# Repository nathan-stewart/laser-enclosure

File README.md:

# Laser Enclosure Fire Control Diagrams

This repository contains Graphviz DOT diagrams for documenting the fire suppression logic and relay control layout in a Raspberry Pi-controlled laser enclosure project.

## Included Files

### `fire_state_machine.dot`
- Describes the FIRE state logic.
- **ARMED**: Tank is pressurized (system ready).
- **FIRE**: Triggered by pressure drop, CO₂ valve opens, gates close.
- **RESET**: Performed via E-stop twist.
- Use `dot -Tpng fire_state_machine.dot -o fire_state_machine.png` to render.

### `power_distribution.dot`
- Updated relay layout with sequential relay numbering:
  - `K1`: Laser
  - `K2`: High Pressure Air (HPA)
  - `K3`: CO₂ Valve
  - `K4`: Blast Gates (intake/exhaust)
  - `K5`: Low Pressure Air (LPA)
  - `K6`: Heater Fan
  - `K7`: Exhaust Fan
  - `K8`: PTC Heater (AC)
- Use `dot -Tpng relay_layout_k3_k4_separated.dot -o relay_layout_k3_k4_separated.png` to render.

## Notes

- Gates are gravity-closing and do not remain activated after a FIRE event.
- CO₂ valve remains open until a manual reset is performed.
- The system arms based on tank pressure and triggers on pressure drop.
- Relays are powered from 24V, 12V, and AC lines as appropriate.

## Rendering

Install [Graphviz](https://graphviz.org/download/) and run:

```bash
dot -Tpng fire_state_machine.dot -o fire_state_machine.png
dot -Tpng power_distribution.dot -o power_distribution.png
```

Or use online editors like [edotor.net](https://edotor.net/) or [dreampuf.github.io](https://dreampuf.github.io/GraphvizOnline/).

---

**Enginerd-built. Fire-tested.** 🔥🛠️

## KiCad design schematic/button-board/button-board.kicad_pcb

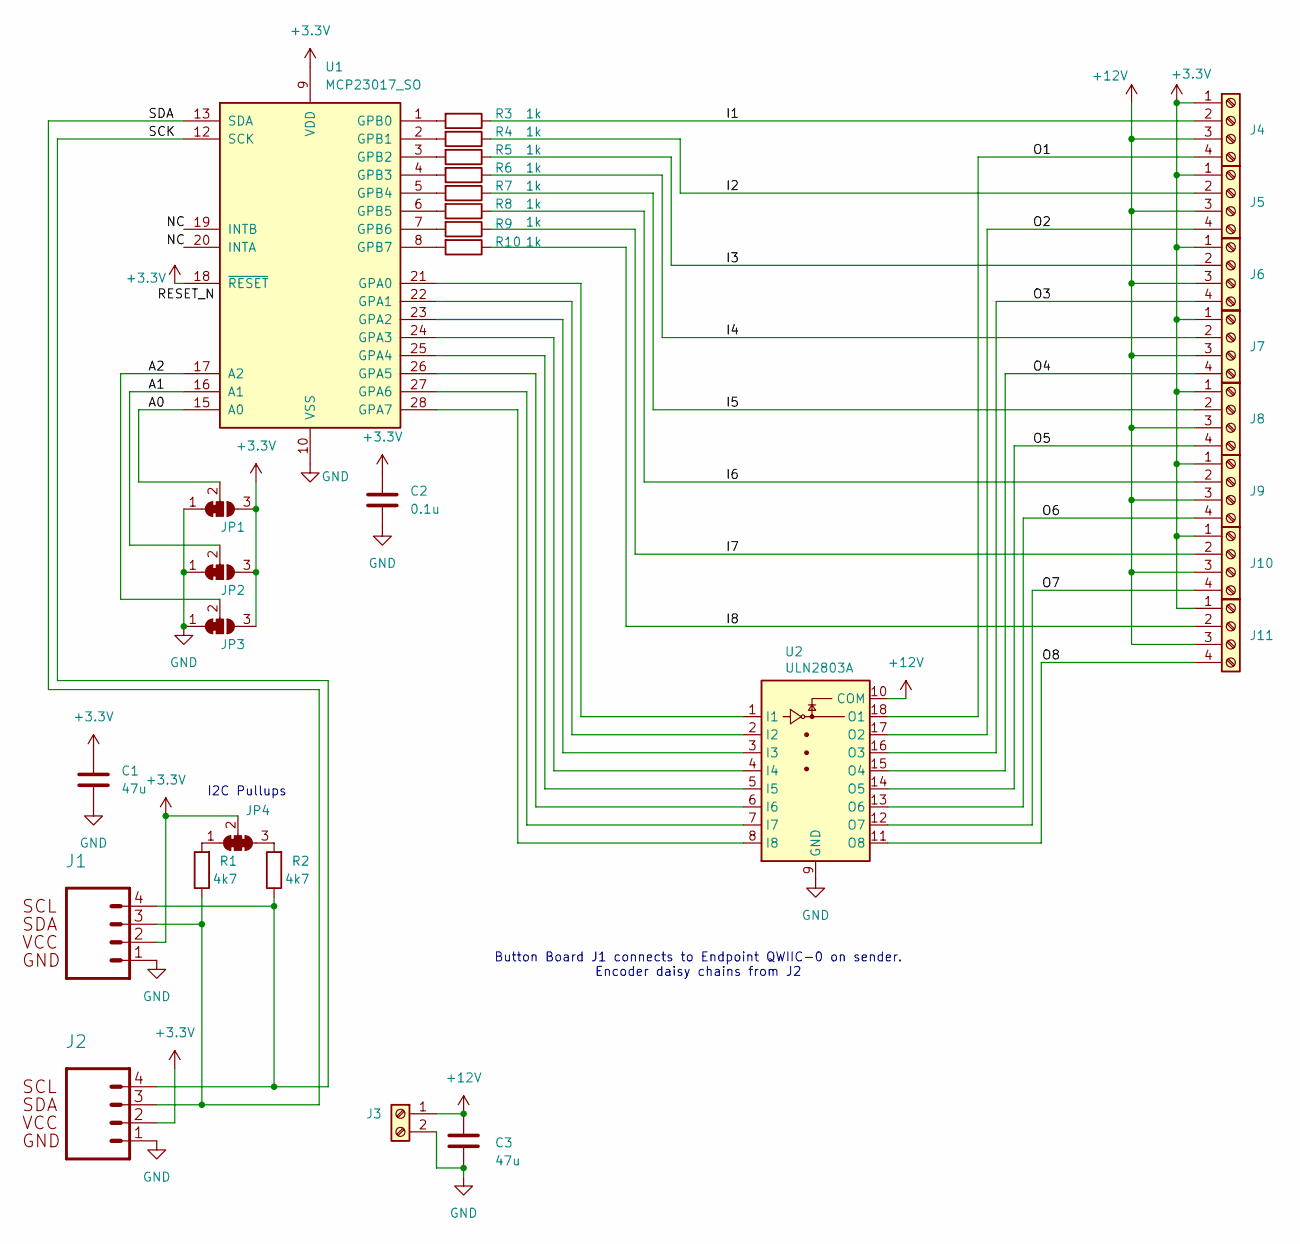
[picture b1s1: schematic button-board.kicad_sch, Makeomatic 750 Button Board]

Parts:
C1, C3: 47u; C_Radial_D6.3mm_H11.0mm_P2.50mm
C2: 0.1u; C_0805_2012Metric
J1, J2: 1x04_RA_SMD
J3: Screw_Terminal_01x02; TerminalBlock_Phoenix_MKDS-1,5-2-5.08_1x02_P5.08mm_Horizont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
J4, J5, J6, J7, J8, J9, J10, J11: Screw_Terminal_01x04; TerminalBlock_Phoenix_MKDS-1,5-4-5.08_1x04_P5.08mm_Horizont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
JP1, JP2, JP3: SolderJumper_3_Bridged12; SolderJumper-3_P1.3mm_Bridged12_RoundedPad1.0x1.5mm_NumberL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
JP4: SolderJumper_3_Bridged123; SolderJumper-3_P1.3mm_Bridged123_RoundedPad1.0x1.5mm_Number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
R1, R2: 4k7; R_0805_2012Metric
R3, R4, R5, R6, R7, R8, R9, R10: 1k; R_0805_2012Metric
U1: MCP23017_SO; SOIC-28W_7.5x17.9mm_P1.27mm
U2: ULN2803A; SOP-18_7.495x11.515mm_P1.27mm

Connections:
+3.3V: C1.1, C2.1, J1.2, J2.2, J4.1, J5.1, J6.1, J7.1, J8.1, J9.1, J10.1, J11.1, JP1.3 (B), JP2.3 (B), JP3.3 (B), JP4.2 (C), U1.9 (VDD), U1.18 (~RESET)
+12V: C3.1, J3.1, J4.3, J5.3, J6.3, J7.3, J8.3, J9.3, J10.3, J11.3, U2.10 (COM)
GND: C1.2, C2.2, C3.2, J1.1, J2.1, J3.2, JP1.1 (A), JP2.1 (A), JP3.1 (A), U1.10 (VSS), U2.9 (GND)
unnamed: J4.2, R3.1
unnamed: J4.4, U2.18 (O1)
unnamed: J5.2, R4.1
unnamed: J5.4, U2.17 (O2)
unnamed: J6.2, R5.1
unnamed: J6.4, U2.16 (O3)
unnamed: J7.2, R6.1
unnamed: J7.4, U2.15 (O4)
unnamed: J8.2, R7.1
unnamed: J8.4, U2.14 (O5)
unnamed: J9.2, R8.1
unnamed: J9.4, U2.13 (O6)
unnamed: J10.2, R9.1
unnamed: J10.4, U2.12 (O7)
unnamed: J11.2, R10.1
unnamed: J11.4, U2.11 (O8)
unnamed: JP1.2 (C), U1.15 (A0)
unnamed: JP2.2 (C), U1.16 (A1)
unnamed: JP3.2 (C), U1.17 (A2)
unnamed: JP4.1 (A), R1.2
unnamed: JP4.3 (B), R2.2
unnamed: U1.21 (GPA0), U2.1 (I1)
unnamed: U1.22 (GPA1), U2.2 (I2)
unnamed: U1.23 (GPA2), U2.3 (I3)
unnamed: U1.24 (GPA3), U2.4 (I4)
unnamed: U1.25 (GPA4), U2.5 (I5)
unnamed: U1.26 (GPA5), U2.6 (I6)
unnamed: U1.27 (GPA6), U2.7 (I7)
unnamed: U1.28 (GPA7), U2.8 (I8)
unnamed: R3.2, U1.1 (GPB0)
unnamed: R4.2, U1.2 (GPB1)
unnamed: R5.2, U1.3 (GPB2)
unnamed: R6.2, U1.4 (GPB3)
unnamed: R7.2, U1.5 (GPB4)
unnamed: R8.2, U1.6 (GPB5)
unnamed: R9.2, U1.7 (GPB6)
unnamed: R10.2, U1.8 (GPB7)
unnamed: J1.4, J2.4, R2.1, U1.12 (SCK)
unnamed: J1.3, J2.3, R1.1, U1.13 (SDA)

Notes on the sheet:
I2C Pullups
Button Board J1 connects to Endpoint QWIIC-0 on sender. Encoder daisy chains from J2

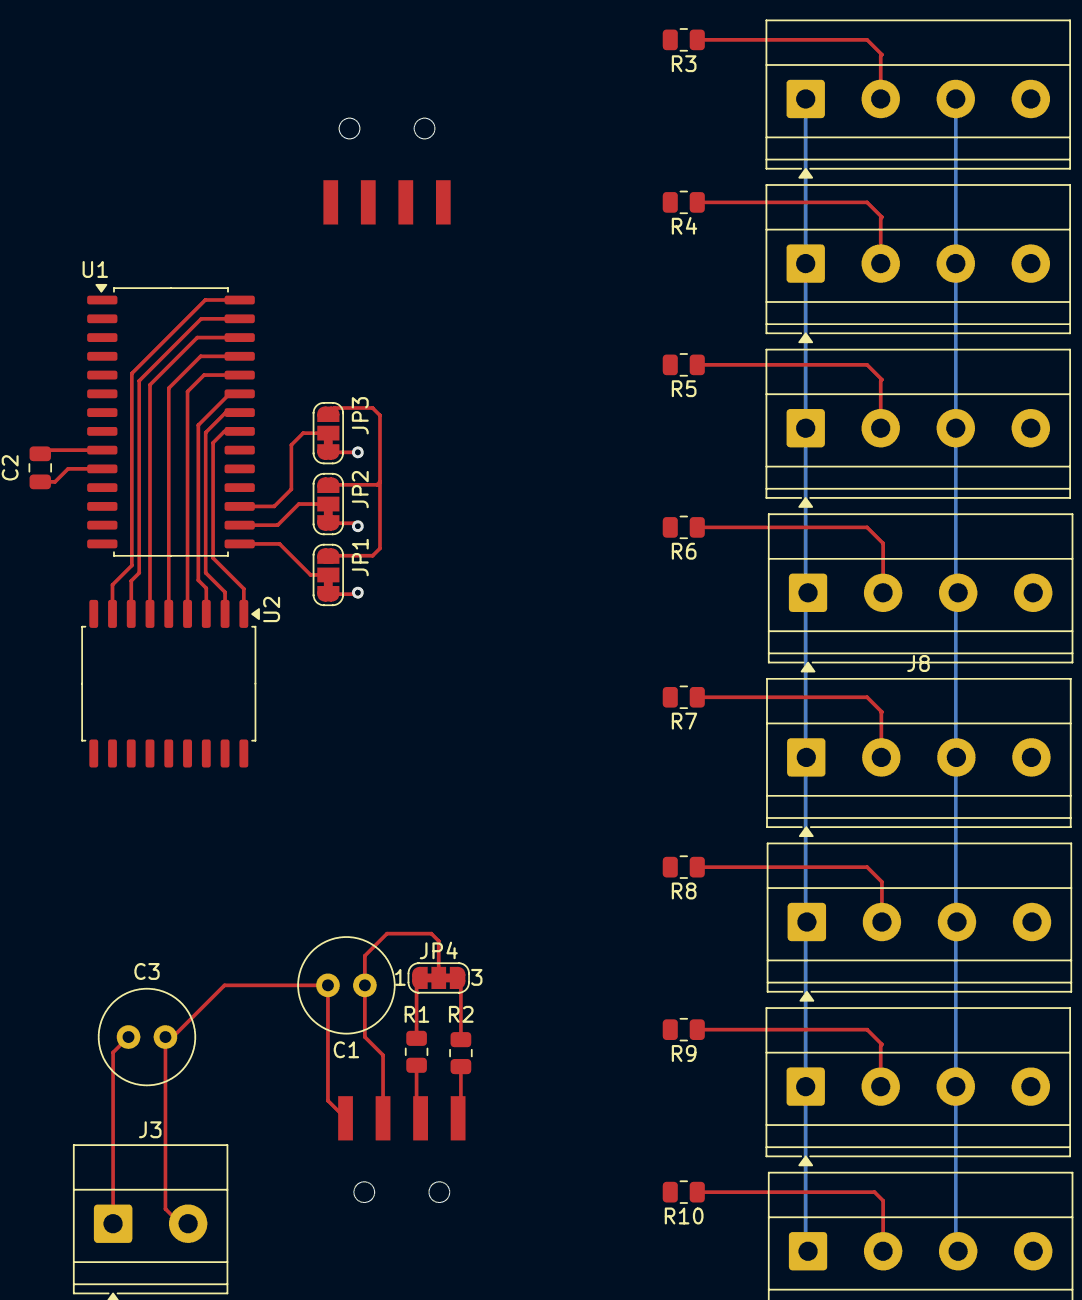
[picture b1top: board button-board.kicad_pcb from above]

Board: 2 copper layers, 30 parts (0 on the bottom side), 42 nets.

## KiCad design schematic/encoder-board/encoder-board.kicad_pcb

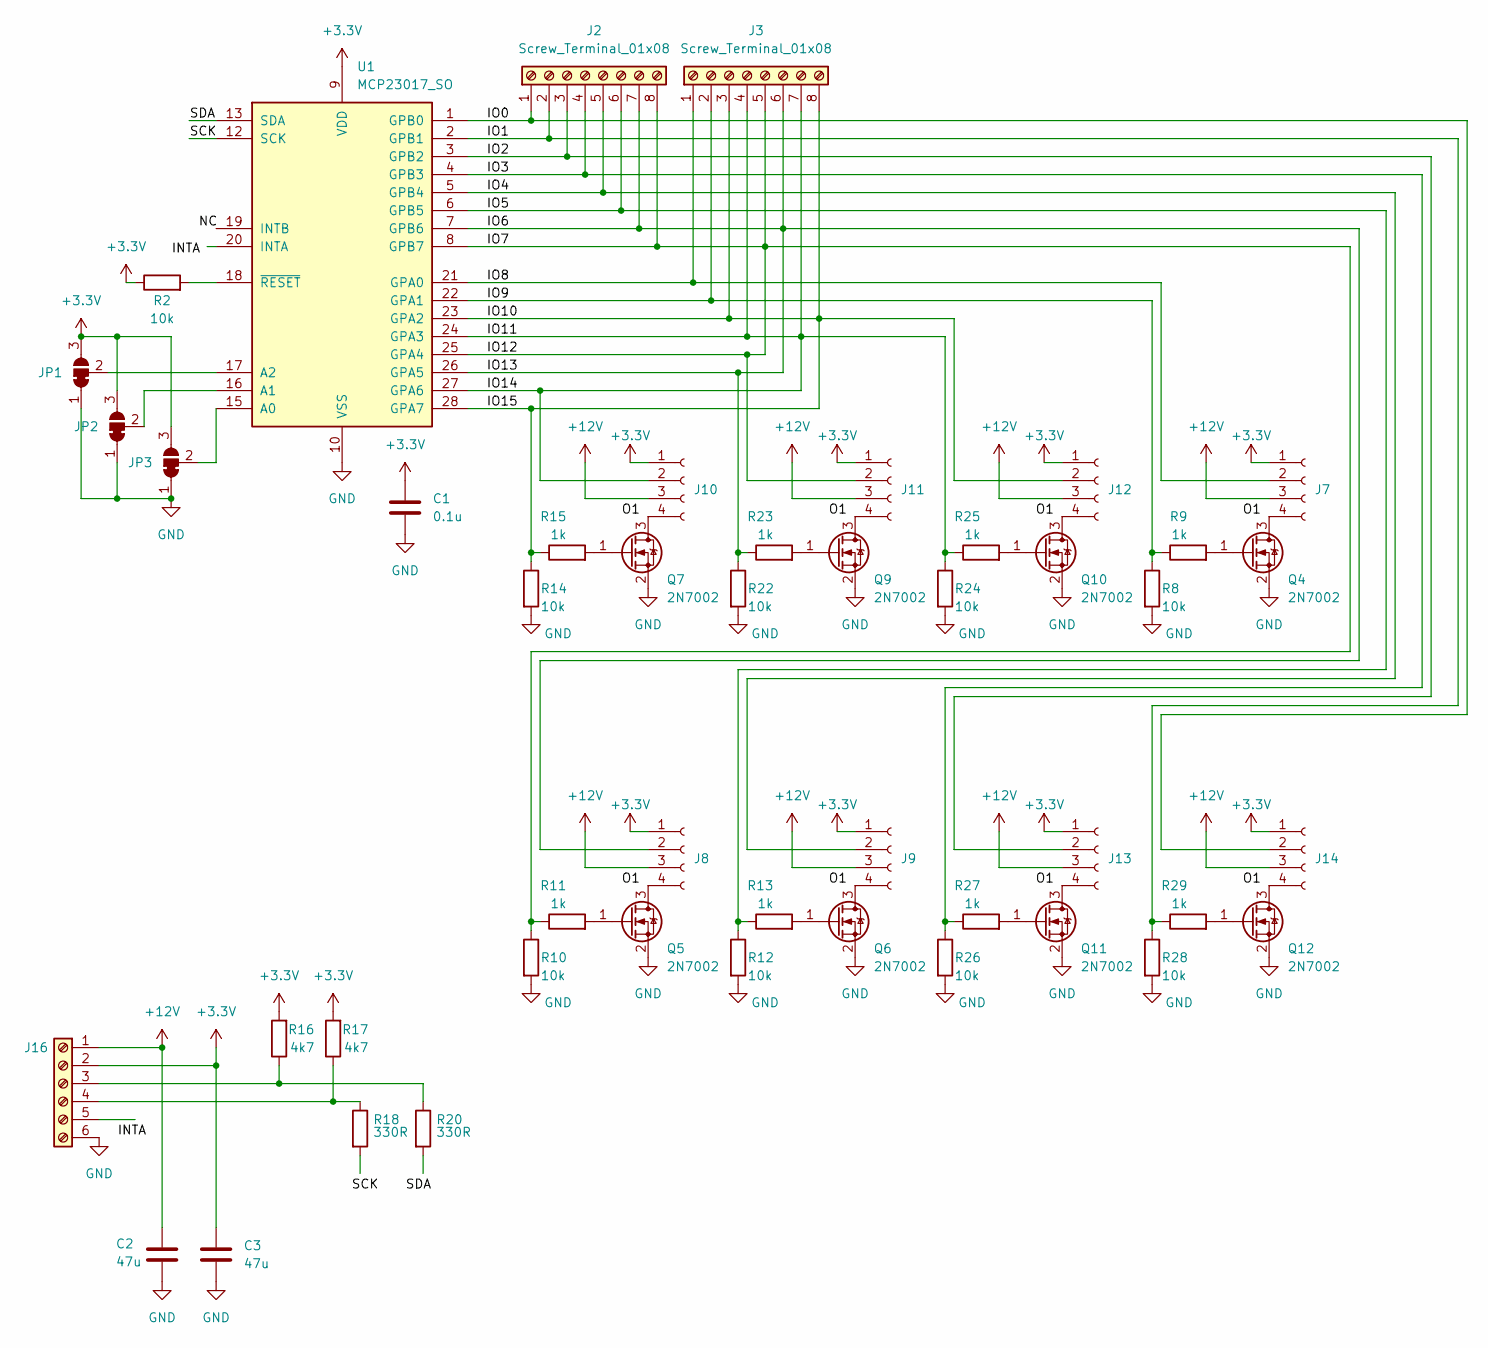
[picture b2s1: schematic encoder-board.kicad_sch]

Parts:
C1: 0.1u; C_0805_2012Metric
C2, C3: 47u; C_Radial_D6.3mm_H11.0mm_P2.50mm
J2, J3: Screw_Terminal_01x08; TerminalBlock_bornier-8_P5.08mm
J7, J8, J9, J10, J11, J12, J13, J14: Conn_01x04_Socket; JST_XH_B4B-XH-AM_1x04_P2.50mm_Vertical
J16: Screw_Terminal_01x06; TerminalBlock_bornier-6_P5.08mm
JP1, JP2, JP3: SolderJumper_3_Bridged12; SolderJumper-3_P1.3mm_Bridged12_RoundedPad1.0x1.5mm
Q4, Q5, Q6, Q7, Q9, Q10, Q11, Q12: 2N7002; SOT-23
R2, R8, R10, R12, R14, R22, R24, R26, R28: 10k; R_0805_2012Metric
R9, R11, R13, R15, R23, R25, R27, R29: 1k; R_0805_2012Metric
R16, R17: 4k7; R_0805_2012Metric
R18, R20: 330R; R_0805_2012Metric
U1: MCP23017_SO; SOIC-28W_7.5x17.9mm_P1.27mm

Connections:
+3.3V: C1.1, C3.1, J7.1, J8.1, J9.1, J10.1, J11.1, J12.1, J13.1, J14.1, J16.2, JP1.3 (B), JP2.3 (B), JP3.3 (B), R2.1, R16.2, R17.2, U1.9 (VDD)
+12V: C2.1, J7.3, J8.3, J9.3, J10.3, J11.3, J12.3, J13.3, J14.3, J16.1
/IO0: J2.1, J14.2, U1.1 (GPB0)
/IO1: J2.2, R28.1, R29.1, U1.2 (GPB1)
/IO2: J2.3, J13.2, U1.3 (GPB2)
/IO3: J2.4, R26.1, R27.1, U1.4 (GPB3)
/IO4: J2.5, J9.2, U1.5 (GPB4)
/IO5: J2.6, R12.1, R13.1, U1.6 (GPB5)
/IO8: J3.1, J7.2, U1.21 (GPA0)
/IO9: J3.2, R8.1, R9.1, U1.22 (GPA1)
/IO10: J3.3, J3.8, J12.2, R14.1, R15.1, U1.23 (GPA2), U1.28 (GPA7)
/IO11: J3.4, J3.7, J10.2, R24.1, R25.1, U1.24 (GPA3), U1.27 (GPA6)
/IO12: J2.8, J3.5, J11.2, R10.1, R11.1, U1.8 (GPB7), U1.25 (GPA4)
/IO13: J2.7, J3.6, J8.2, R22.1, R23.1, U1.7 (GPB6), U1.26 (GPA5)
/SCK: U1.12 (SCK)
/SDA: U1.13 (SDA)
GND: C1.2, C2.2, C3.2, J16.6, JP1.1 (A), JP2.1 (A), JP3.1 (A), Q4.2 (S), Q5.2 (S), Q6.2 (S), Q7.2 (S), Q9.2 (S), Q10.2 (S), Q11.2 (S), Q12.2 (S), R8.2, R10.2, R12.2, R14.2, R22.2, R24.2, R26.2, R28.2, U1.10 (VSS)
unnamed: J7.4, Q4.3 (D)
unnamed: J8.4, Q5.3 (D)
unnamed: J9.4, Q6.3 (D)
unnamed: J10.4, Q7.3 (D)
unnamed: J11.4, Q9.3 (D)
unnamed: J12.4, Q10.3 (D)
unnamed: J13.4, Q11.3 (D)
unnamed: J14.4, Q12.3 (D)
unnamed: J16.3, R16.1, R20.1
unnamed: J16.4, R17.1, R18.1
unnamed: JP1.2 (C), U1.17 (A2)
unnamed: JP2.2 (C), U1.16 (A1)
unnamed: JP3.2 (C), U1.15 (A0)
unnamed: Q4.1 (G), R9.2
unnamed: Q5.1 (G), R11.2
unnamed: Q6.1 (G), R13.2
unnamed: Q7.1 (G), R15.2
unnamed: Q9.1 (G), R23.2
unnamed: Q10.1 (G), R25.2
unnamed: Q11.1 (G), R27.2
unnamed: Q12.1 (G), R29.2
unnamed: R2.2, U1.18 (~RESET)

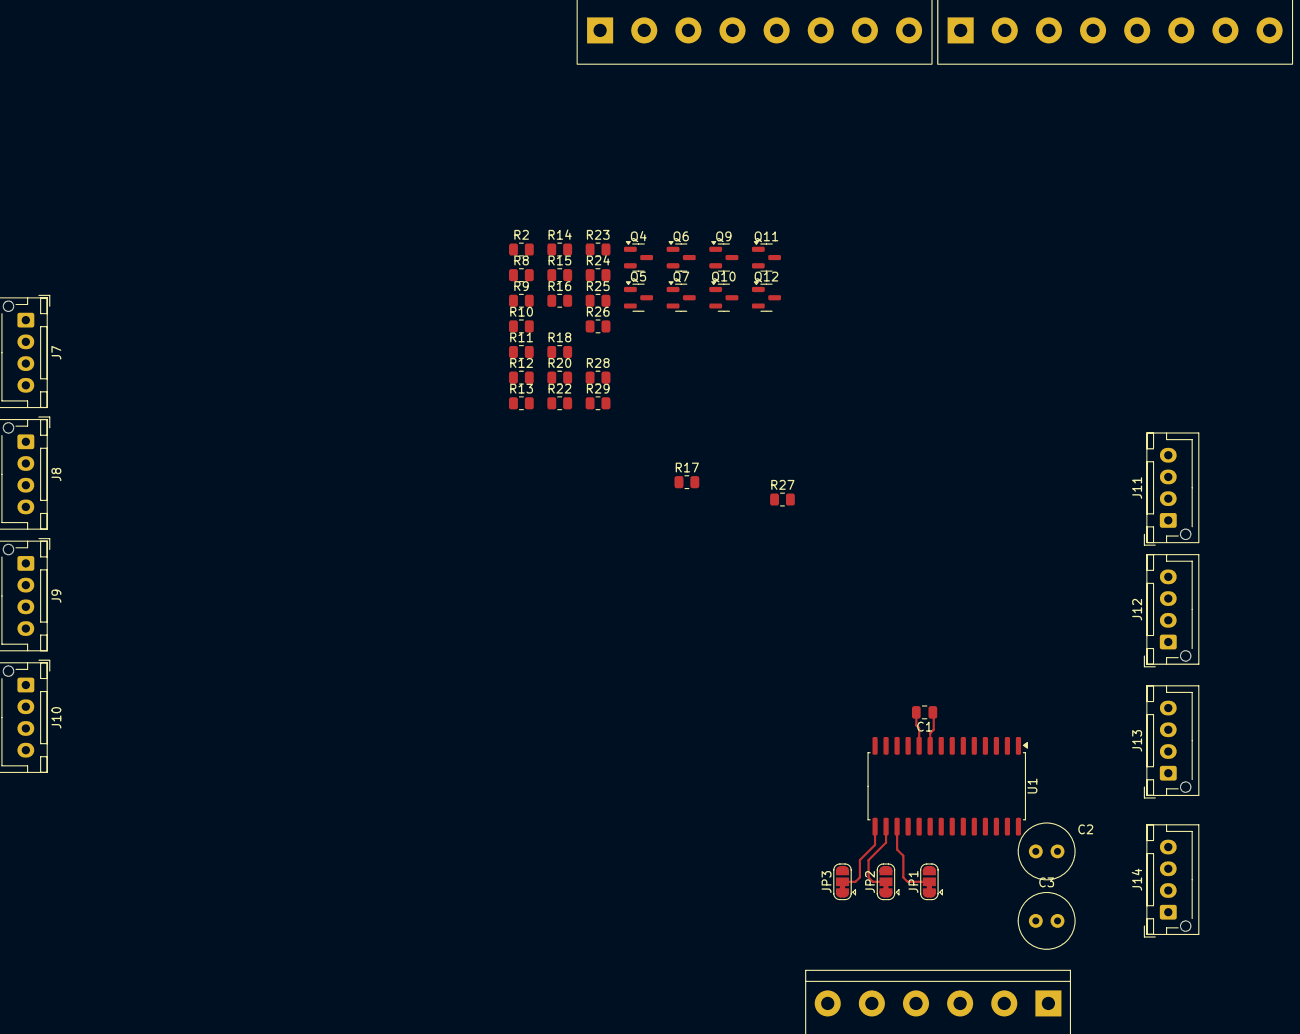
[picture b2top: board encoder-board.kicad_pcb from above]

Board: 2 copper layers, 47 parts (0 on the bottom side), 37 nets.

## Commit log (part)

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2024-06-09 initial setup
2024-06-10 tweaks to back
2024-06-11 major changes to enclosure and rework of machine
2024-06-12 added new files
2024-06-12 updates to 1/4 in thick plywood
2024-06-12 renamed speadsheet (machine will have its own)
2024-06-12 spreadsheet updates
2024-06-13 spreadsheet updates, working on ducting
2024-06-14 changing duct system over to floor
2024-06-15 added exhaust plenum, gate, elbow
2024-06-15 tweaks to the basE
2024-06-15 intake tweaks
2024-06-16 lid cleanup
2024-07-03 tweaks to base, air assist
2025-03-06 rework in progress
2025-03-17 new files
2025-03-24 air duct changes
2025-03-26 updates to base
2025-03-28 updates to lid
2025-03-30 update leg size to existing stock
2025-03-30 reworking the enclosure
2025-03-31 reworking enclosure
2025-03-31 housing updates
2025-03-31 resizing base
2025-04-02 updates to as-built frame
2025-04-02 added foamcore duct
2025-04-03 fixed some ehaust assemblies
2025-04-17 added panel and control block
2025-04-18 don't keep hash in versioned file
2025-04-18 two panel layout - separating hatching to a separate file
2025-04-20 reworked panel icons
2025-04-20 Dr No icon
2025-04-21 laser-setup.yaml
2025-04-21 initial playbook setup
2025-04-21 panel icon rework
2025-04-21 ansible tweaks
2025-04-23 updates to panel and guts
2025-04-23 switched to 21" panels
2025-04-23 moved emergency to switch panel to free up real estate
2025-04-23 removed a bunch of software controlled swithes, rebalanced panesl
2025-04-23 final tweaks
2025-04-23 reoriented layout, moved PEM to bottom
2025-04-24 added spacer and bezel
2025-04-24 wayland removal fixes
2025-04-24 panel tweaks
2025-04-24 create loopback video device
2025-04-25 rotated parts, started inletting for penetrations
2025-04-25 added scale control, boxing for jog
2025-04-25 got loopback video working, services
2025-04-25 fixed estop hole
2025-04-25 reworked layout, split out a burn file
2025-04-25 updated warning zone
2025-04-25 added zero set button, icons for actions
2025-04-26 split boards
2025-04-26 preparing panel for burning
2025-04-26 made meerkat a service
2025-04-27 checked in encoder-mount file
2025-04-27 test cuts, control layout
2025-04-28 fixed pem, 12v, relays, encoder, fuse block, 5v
2025-04-29 tweaks to hole tests, created panel suppport profile
2025-05-03 final version of din mount cutouts
2025-05-03 added tplink board
2025-05-05 added ADC, fixed usb
2025-05-05 added adc board
2025-05-06 moved panel support box to freecad
2025-05-06 updated layout for support avoidance
2025-05-07 go to electronic fire extinguisher button
2025-05-08 reworking panel for finger support
2025-05-08 tweaks to panels
2025-05-09 panel updates
2025-05-10 mirrored to get the ends right
2025-05-19 part to build - working on cam now
2025-05-19 ready to cut
2025-05-27 updates to panel
2025-05-27 added ioboard
2025-05-28 panel tweak - moving to soft buttons
2025-05-29 started work on gpio service
2025-05-29 gpio stuff
2025-05-29 restructured ansible
2025-05-29 reworked ansible, added todo
2025-05-30 added write
2025-05-30 ansible updates for deployment
2025-05-30 fixed splash path
2025-05-30 fixed host, added cmdline.txt
2025-05-30 moved splash
2025-05-30 added control board mount cuts to git
2025-05-31 file cleanup
2025-05-31 fixed bad cmdline that broke things
2025-06-05 accept my changes
2025-06-06 removed debian /boot/firmware crap so update-initramfs doesn't break
2025-06-06 ansible cleanup
2025-06-06 fixed splash clause
2025-06-06 venv cleanup
2025-06-06 don't reinstall meerkat if already done
2025-06-06 removed stale targets
2025-06-07 meerkat service
2025-06-08 renamed gpio_service to hal, added ads1115, made packages system wide
2025-06-11 updates - ads1115
2025-06-13 split mcp stuff out
2025-06-14 rework inputs
2025-06-15 service rework
2025-06-15 switch dht11 libs
2025-06-16 hal service cleanup
2025-06-17 service updates
2025-06-17 create /opt/kiosk
2025-06-17 moved mcp back into hal
2025-06-17 graceful thread exit
2025-06-17 added client to watch zmq
2025-06-17 get initial state
2025-06-17 add service stubs
2025-06-18 zmq updates
2025-06-19 update pins
2025-06-20 major cleanup
2025-06-21 cleanup
2025-06-21 pin changes for dht11
2025-06-21 fixed gpio output
2025-06-21 debugging messages
2025-06-21 thread handling, logging
2025-06-21 clean missing device handling and rescan
2025-06-21 thread cleanup
2025-06-22 added debounce, fixed expander bug
2025-06-22 removed stale zmq_send
2025-06-22 topic tweaking
2025-06-22 send updates at 40hz
2025-06-22 Temp poll 60s
2025-06-22 business logic
2025-06-23 reordered some inputs, apply logic rules
2025-06-23 added control service
2025-06-23 control debug
2025-06-24 fixed dehumidifier code
2025-06-28 added relay test script
2025-06-29 reorganized python
2025-07-01 fixed v4l, removed loopback
2025-07-01 zmq, fixed hal service, buttons
2025-07-01 layout tweaks
2025-07-01 fixed paths/mains
2025-07-01 add logging args
2025-07-01 fixes to gui
2025-07-01 fixed meerkat args
2025-07-01 fix startup files
2025-07-01 fixed to login/startx
2025-07-01 fix gui path
2025-07-02 added idle check, removed stale services
2025-07-02 add heartbeat to shut down laser if control died
2025-07-03 removed get_State
2025-07-03 fixed warnings, errors in services
2025-07-03 added encoder board
2025-07-03 encoder board first pass
2025-07-10 schematic updates
2025-07-10 renamed board
2025-07-10 removed file from git
2025-07-10 added gitignore
2025-07-10 added sparkfun libs
2025-07-10 sparkfun repo
2025-07-11 finalized button board, added sensor board
2025-07-11 sparkfun qwiic endpoint
2025-07-11 added sensor board
2025-07-11 replaced individual transistors with array
2025-07-13 layout work
2025-07-13 updated gitignore
2025-07-13 updated net labels for pcb layout, added sender board
2025-07-13 added pico i2c test
2025-07-14 converted hal to use bme23017, only one ADS1115 now, still two MCP23017 but in a map
2025-07-14 add the encoder to the 40hz polling
2025-07-14 likely broken but rewrite of missing device handling
2025-07-14 i2c cleanup
2025-07-15 start the watchdogs to shut down the laser if control isn't running
2025-07-18 started rework for mock devices
2025-07-18 fixed syntax on expanders
2025-07-18 added encoder wrapper
2025-07-18 mock updates
2025-07-18 make config safe to call after config
2025-07-19 removed pinamap - created mockable interface for gpio
2025-07-19 ongoing work
2025-07-20 rework of mock device system
2025-07-20 mock rework continued
2025-07-20 removed pin class
2025-07-20 named threads
2025-07-21 mock rework fixes
2025-07-21 cleanup of refactor
2025-07-22 fixed to expander
2025-07-22 fixed i2c addr in real devices
2025-07-22 added EMA filtering to analog
2025-07-22 fixed read/debounce
2025-07-22 moving debounce into class
2025-07-22 filtering/debounce
2025-07-23 fixed gpio debounce
2025-07-23 updates to read methods
2025-07-23 removed now thin functions
2025-07-23 switched to yields
2025-07-23 yield updates
2025-07-24 fixed monitor thread launch
2025-07-24 fixed set_outputs to new mechanism
2025-07-24 fixed double queue, turn generators into dicts for remaining devices
2025-07-24 fixed systemd notifier
2025-07-24 fixed missing outputs if no inputs received
2025-07-24 fixed set_output message reply objects
2025-07-24 added prefixes back, updated control to match hal changes
2025-07-24 populate state struct so missing in/outs don't mess up control - it's sorta simple
2025-07-25 brightness not suppored - use hdmi power
2025-07-26 working on display blanking
2025-07-26 generator fixes
2025-07-26 restart services after deploy
2025-07-26 fixed missing vars
2025-07-26 fixed din leg holes
2025-07-27 meerkat settings
2025-07-27 removed environment panel
2025-07-27 started work on remote execution
2025-07-28 refactored to run on x86
2025-07-28 added sender board
2025-07-28 inverted logic for rpi gpios
2025-08-04 fixed services so they start properly
2025-08-04 added gpios to config.txt, restart only on change
2025-08-06 fixed typo in camera stream
2025-08-08 fixed register for restarts, fixed run_gui
2025-08-10 migration cleanup
2025-08-10 library import partial fixes
2025-08-10 fixed additional circuitpython imports
2025-08-10 made mock consistent with real, fixed debounce bugs
2025-08-10 add channel limit to adc
2025-08-10 fixed analog reads
2025-08-11 adc now working
2025-08-11 lock configuration after config
2025-08-12 changes to configure
2025-08-13 config now idempotent, reconnects if lost
2025-08-13 cleaned up label
2025-08-13 fixed stray after clause
2025-08-13 make dehumidifier just use RH instead of dewpoint
2025-08-13 log devices on config
2025-08-13 added graceful shutdown handling
2025-08-15 fied lock issue with control message
2025-08-16 WIP - dewpoint
2025-08-16 WIP - apply rules change
2025-08-16 lambda fixes
2025-08-16 added virtual outputs to tie fan/heater togther
2025-08-16 hal updates for virtuals
2025-08-16 fixed handle commands
2025-08-16 updated dryer params
2025-08-16 layout change to app
2025-08-18 reworked virtual gpio system - WIP
2025-08-18 removed stale file
2025-08-18 fix encoder bug
2025-08-18 fixed bug in encoder, watchdog
2025-08-18 renamed gpio instance to rpi_gpios to avoid shadowing
2025-08-18 renamed o_dehumidifier to o_dryer, added logging
2025-08-18 fixed but in set_output
2025-08-19 fix state for virtuals
2025-08-19 debugging slaved pin polarity
2025-08-19 make gpio read tolerant of pin inputs
2025-08-19 added injection command
2025-08-19 update to inject command
2025-08-20 fixed neopixel light
2025-08-20 fixed debug out for gpio writes
2025-08-20 fixed output polarity
2025-08-20 removed virtual_outputs and combined heater/fan with a single ac device
2025-08-20 fixed service files
2025-08-20 removed virtual gpios, fixed bug in dryer
2025-08-23 added panel mount for solenoid plugs
2025-08-23 cleaned up for cutting
2025-08-23 inlet acrylic, add labels, reduce wood holes to screw size
2025-08-24 updates to plug templates
2025-08-24 updated cut file
2025-08-24 new router template
2025-08-24 started combining boards
2025-08-28 combined plug panels
2025-09-05 acrylic etch face
2025-09-05 added router template for plug panel
2025-09-05 cut template
2025-09-24 made a vcarve/drill version in aluminum
2025-09-24 updated paths
2025-12-28 reworked bottom panel in aluminum, allow more space for gx12 plugs
2026-01-25 picking up again - jan 2026
2026-05-13 removing headless meerkat idea and gui, keeping hal/control layer
2026-05-13 changed install dir for utils
2026-05-14 added virtual devices
2026-05-14 replaced inject with halctl
2026-05-15 added ability to set virtual inputs from halctl
2026-05-15 fixed bug in halctl/virtuals
2026-05-15 WIP - purge model changing
2026-05-16 fixed bug in purge timing
2026-05-16 fixed v_purge bug
2026-06-05 make sure we check status against last commanded
2026-06-11 Added LPA back for aquarium pump/side jet
2026-06-21 major rework - relays, panel, new command structure, meerk40t module
2026-06-21 removed files in reorg
2026-06-21 fixed args in meerk40t plugin
